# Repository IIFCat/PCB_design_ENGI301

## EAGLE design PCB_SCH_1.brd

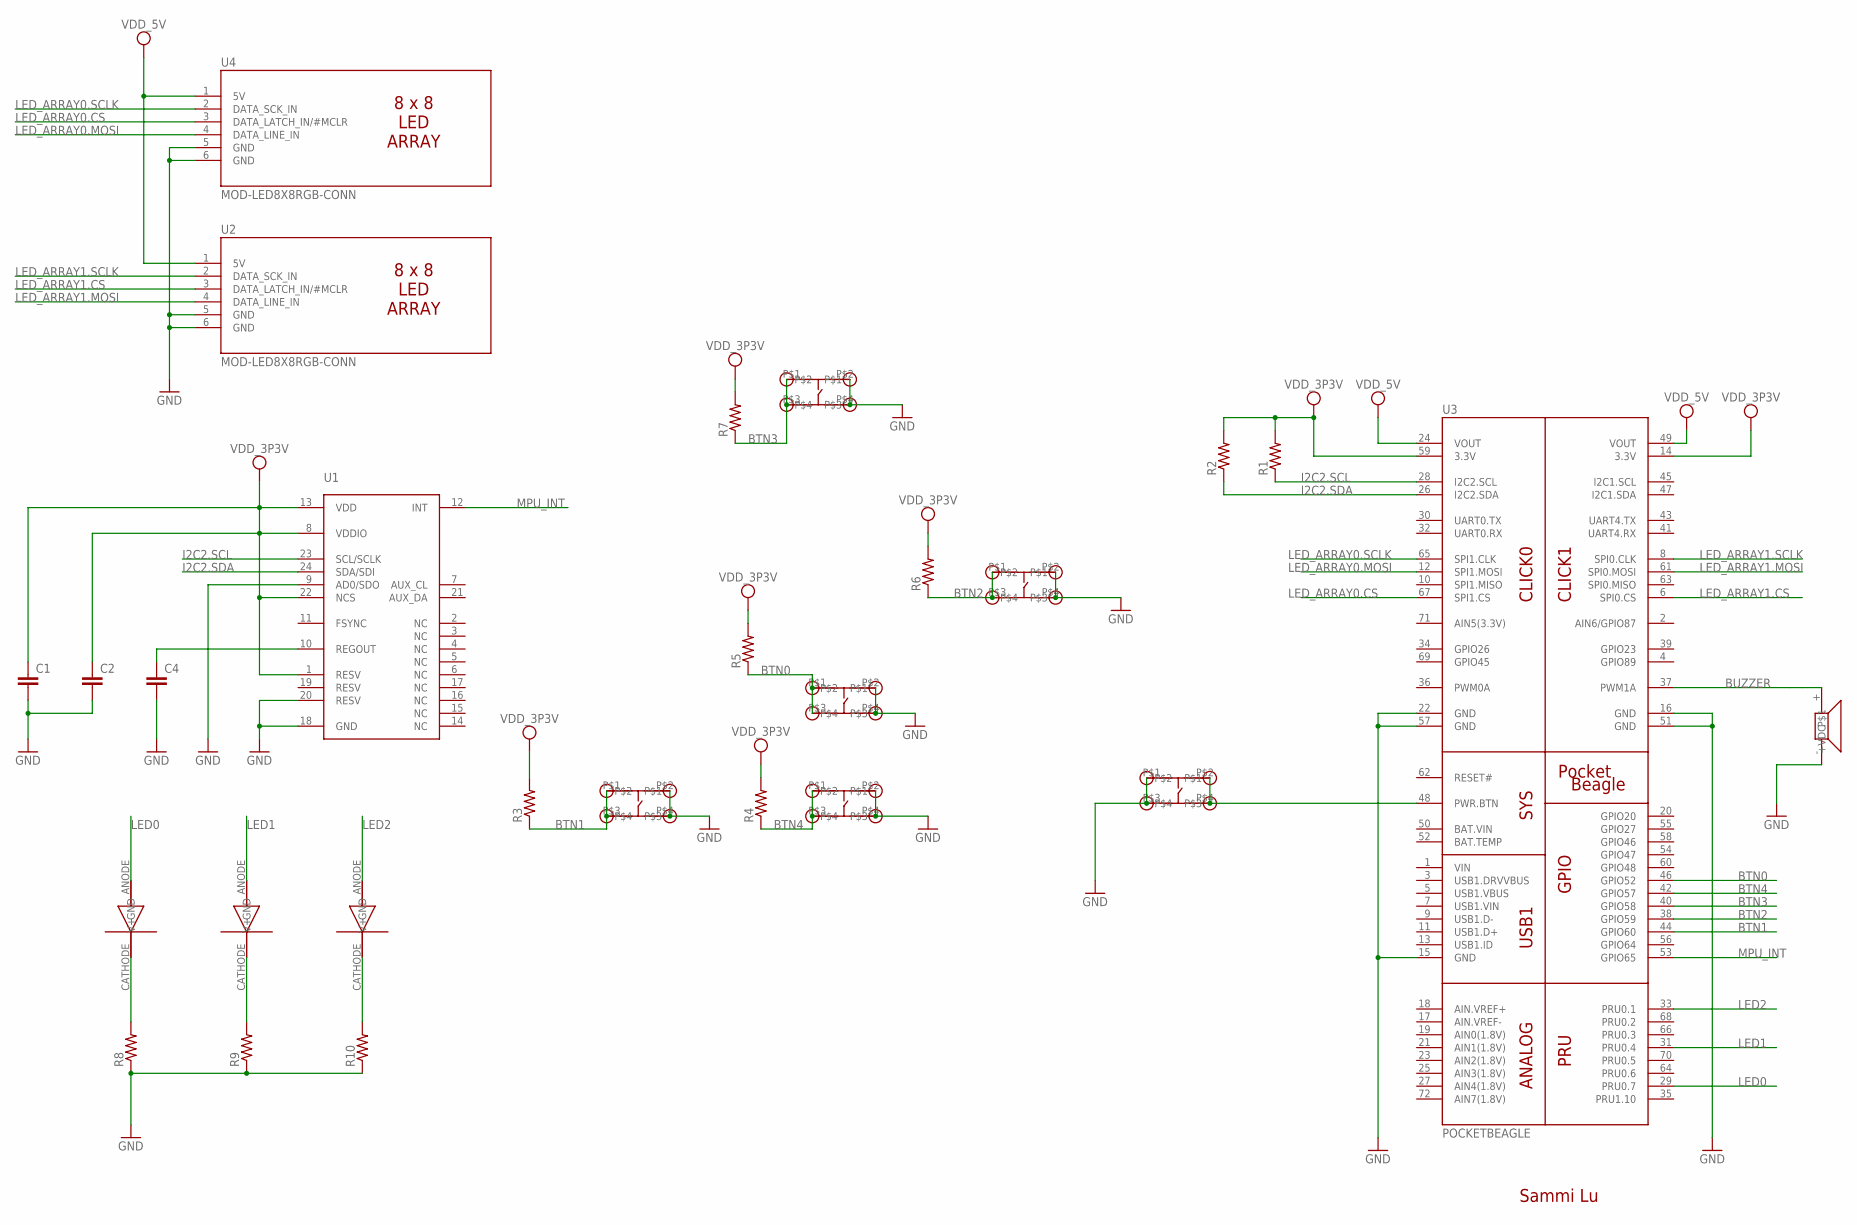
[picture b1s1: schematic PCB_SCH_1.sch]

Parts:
BUTTON0, BUTTON1, BUTTON2, BUTTON3, BUTTON4, BUTTON5: BUTTON_; 115*117
C1, C2, C4: C_C0603; C0603
LED0, LED1, LED2: LTST_; 1.6*0.8
R1, R2, R3, R4, R5, R6, R7: R_R2012; R2012
R8, R9, R10: R_R1005; R1005
U1: MPU_9250; QFN-3MM*3MM
U2, U4: MOD-LED8X8RGB-CONN; FE06W
U3: POCKETBEAGLE
U$1: BUZZER_; 12CIRCLE

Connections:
BTN0: BUTTON0.P$1, BUTTON0.P$3, R5.1, U3.46 (GPIO52)
BTN1: BUTTON1.P$1, BUTTON1.P$3, R3.1, U3.44 (GPIO60)
BTN2: BUTTON2.P$1, BUTTON2.P$3, R6.1, U3.38 (GPIO59)
BTN3: BUTTON3.P$1, BUTTON3.P$3, R7.1, U3.40 (GPIO58)
BTN4: BUTTON4.P$1, BUTTON4.P$3, R4.1, U3.42 (GPIO57)
BUZZER: U3.37 (PWM1A), U$1.+ (+VDC)
GND: BUTTON0.P$2, BUTTON0.P$4, BUTTON1.P$2, BUTTON1.P$4, BUTTON2.P$2, BUTTON2.P$4, BUTTON3.P$2, BUTTON3.P$4, BUTTON4.P$2, BUTTON4.P$4, BUTTON5.P$1, BUTTON5.P$3, C1.2, C2.2, C4.2, R8.1, R9.1, R10.1, U1.9 (AD0/SDO), U1.18 (GND), U1.20 (RESV), U2.5 (GND), U2.6 (GND), U3.15 (GND), U3.16 (GND), U3.48 (PWR.BTN), U3.51 (GND), U4.5 (GND), U4.6 (GND), U$1.-
I2C2.SCL: R1.1, U1.23 (SCL/SCLK), U3.28 (I2C2.SCL)
I2C2.SDA: R2.1, U1.24 (SDA/SDI), U3.26 (I2C2.SDA)
LED0: LED0.ANODE (V+), U3.29 (PRU0.7)
LED1: LED1.ANODE (V+), U3.31 (PRU0.4)
LED2: LED2.ANODE (V+), U3.33 (PRU0.1)
LED_ARRAY0.CS: U3.67 (SPI1.CS), U4.3 (DATA_LATCH_IN/#MCLR)
LED_ARRAY0.MOSI: U3.12 (SPI1.MOSI), U4.4 (DATA_LINE_IN)
LED_ARRAY0.SCLK: U3.65 (SPI1.CLK), U4.2 (DATA_SCK_IN)
LED_ARRAY1.CS: U2.3 (DATA_LATCH_IN/#MCLR), U3.6 (SPI0.CS)
LED_ARRAY1.MOSI: U2.4 (DATA_LINE_IN), U3.61 (SPI0.MOSI)
LED_ARRAY1.SCLK: U2.2 (DATA_SCK_IN), U3.8 (SPI0.CLK)
MPU_INT: U1.12 (INT), U3.53 (GPIO65)
unnamed: BUTTON5.P$2, BUTTON5.P$4, U3.22 (GND), U3.57 (GND)
unnamed: C4.1, U1.10 (REGOUT)
unnamed: LED0.CATHODE (GND), R8.2
unnamed: LED1.CATHODE (GND), R9.2
unnamed: LED2.CATHODE (GND), R10.2
SYS_VDD1_3P3V: C1.1, C2.1, R1.2, R2.2, R3.2, R4.2, R5.2, R6.2, R7.2, U1.1 (RESV), U1.8 (VDDIO), U1.13 (VDD), U1.22 (NCS), U3.14 (3.3V), U3.59 (3.3V)
VDD_5V: U2.1 (5V), U3.24 (VOUT), U3.49 (VOUT), U4.1 (5V)

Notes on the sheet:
Sammi Lu

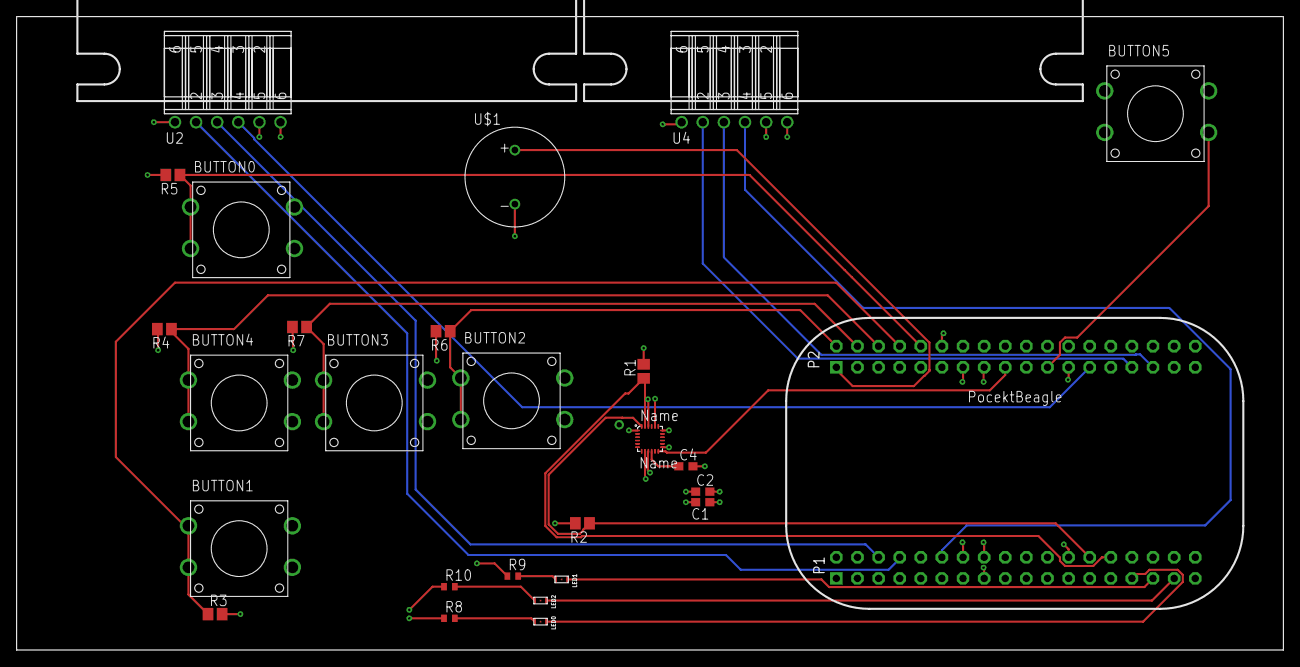
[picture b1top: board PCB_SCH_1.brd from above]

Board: 2 copper layers, 152.4 x 76.2 mm, 29 parts (0 on the bottom side), 26 nets.

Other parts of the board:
U$2, U$3: MOD-LED8X8RGB
